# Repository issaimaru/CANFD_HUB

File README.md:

# CANFD_HUB
CANFDコントローラ「ひなた」用のハブ<br>
<br>

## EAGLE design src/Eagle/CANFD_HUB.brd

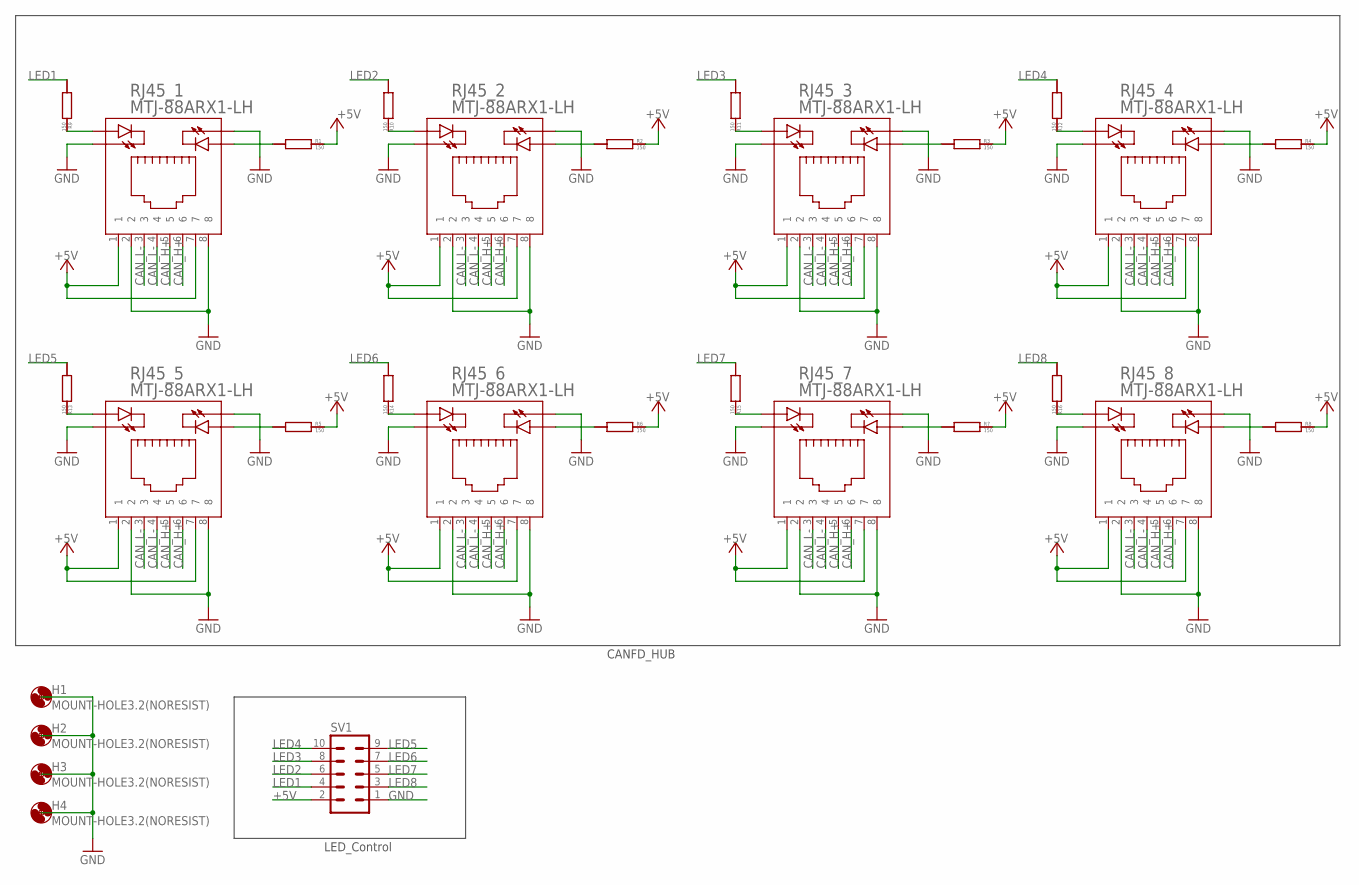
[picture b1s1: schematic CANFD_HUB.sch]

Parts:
H1, H2, H3, H4: MOUNT-HOLE3.2(NORESIST); 3,2
R1, R2, R3, R4, R5, R6, R7, R8, R9, R10, R11, R12, R13, R14, R15, R16: 150; CR0603
RJ45_1, RJ45_2, RJ45_3, RJ45_4, RJ45_5, RJ45_6, RJ45_7, RJ45_8: MTJ-88ARX1-LH
SV1: ML10

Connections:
+5V: R1.RIGHT, R2.RIGHT, R3.RIGHT, R4.RIGHT, R5.RIGHT, R6.RIGHT, R7.RIGHT, R8.RIGHT, RJ45_1.1, RJ45_1.7, RJ45_2.1, RJ45_2.7, RJ45_3.1, RJ45_3.7, RJ45_4.1, RJ45_4.7, RJ45_5.1, RJ45_5.7, RJ45_6.1, RJ45_6.7, RJ45_7.1, RJ45_7.7, RJ45_8.1, RJ45_8.7, SV1.2
CAN_H+: RJ45_1.5, RJ45_1.6, RJ45_2.5, RJ45_2.6, RJ45_3.5, RJ45_3.6, RJ45_4.5, RJ45_4.6, RJ45_5.5, RJ45_5.6, RJ45_6.5, RJ45_6.6, RJ45_7.5, RJ45_7.6, RJ45_8.5, RJ45_8.6
CAN_L-: RJ45_1.3, RJ45_1.4, RJ45_2.3, RJ45_2.4, RJ45_3.3, RJ45_3.4, RJ45_4.3, RJ45_4.4, RJ45_5.3, RJ45_5.4, RJ45_6.3, RJ45_6.4, RJ45_7.3, RJ45_7.4, RJ45_8.3, RJ45_8.4
GND: H1.P$1, H2.P$1, H3.P$1, H4.P$1, RJ45_1.2, RJ45_1.8, RJ45_1.LED1_K, RJ45_1.LED2_K, RJ45_2.2, RJ45_2.8, RJ45_2.LED1_K, RJ45_2.LED2_K, RJ45_3.2, RJ45_3.8, RJ45_3.LED1_K, RJ45_3.LED2_K, RJ45_4.2, RJ45_4.8, RJ45_4.LED1_K, RJ45_4.LED2_K, RJ45_5.2, RJ45_5.8, RJ45_5.LED1_K, RJ45_5.LED2_K, RJ45_6.2, RJ45_6.8, RJ45_6.LED1_K, RJ45_6.LED2_K, RJ45_7.2, RJ45_7.8, RJ45_7.LED1_K, RJ45_7.LED2_K, RJ45_8.2, RJ45_8.8, RJ45_8.LED1_K, RJ45_8.LED2_K, SV1.1
LED1: R9.LEFT, SV1.4
LED2: R10.LEFT, SV1.6
LED3: R11.LEFT, SV1.8
LED4: R12.LEFT, SV1.10
LED5: R13.LEFT, SV1.9
LED6: R14.LEFT, SV1.7
LED7: R15.LEFT, SV1.5
LED8: R16.LEFT, SV1.3
unnamed: R2.LEFT, RJ45_2.LED2_A
unnamed: R1.LEFT, RJ45_1.LED2_A
unnamed: R3.LEFT, RJ45_3.LED2_A
unnamed: R4.LEFT, RJ45_4.LED2_A
unnamed: R5.LEFT, RJ45_5.LED2_A
unnamed: R6.LEFT, RJ45_6.LED2_A
unnamed: R7.LEFT, RJ45_7.LED2_A
unnamed: R8.LEFT, RJ45_8.LED2_A
unnamed: R9.RIGHT, RJ45_1.LED1_A
unnamed: R10.RIGHT, RJ45_2.LED1_A
unnamed: R11.RIGHT, RJ45_3.LED1_A
unnamed: R12.RIGHT, RJ45_4.LED1_A
unnamed: R13.RIGHT, RJ45_5.LED1_A
unnamed: R14.RIGHT, RJ45_6.LED1_A
unnamed: R15.RIGHT, RJ45_7.LED1_A
unnamed: R16.RIGHT, RJ45_8.LED1_A

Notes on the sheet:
LED_Control
CANFD_HUB

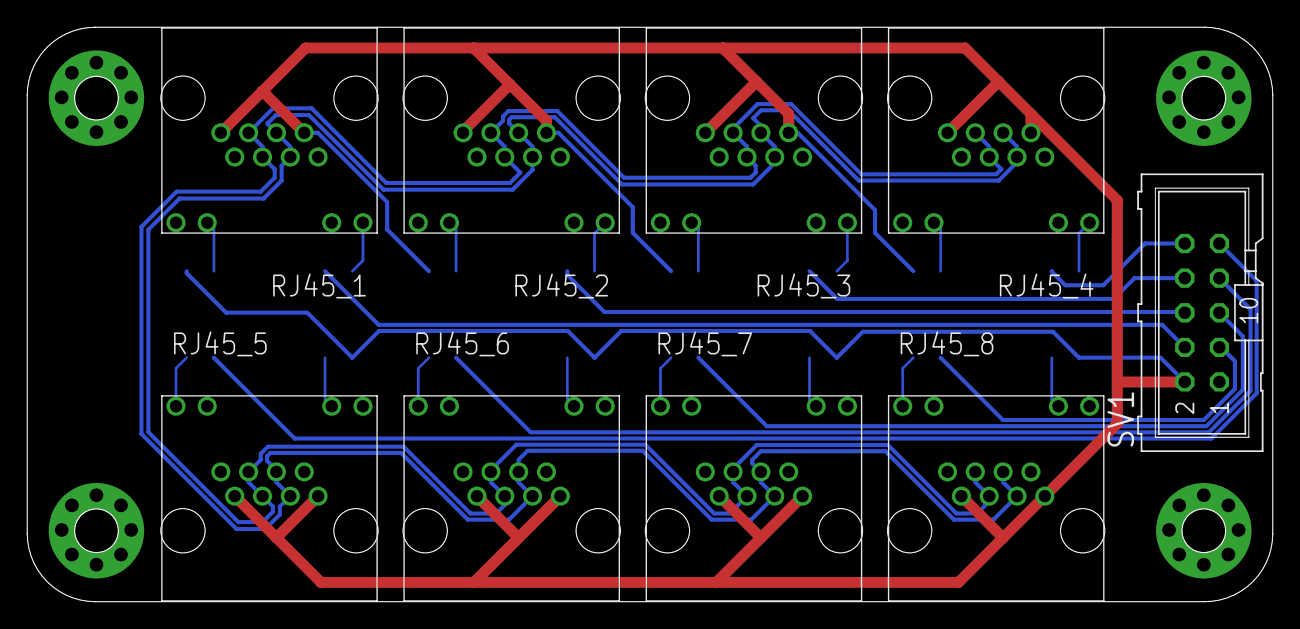
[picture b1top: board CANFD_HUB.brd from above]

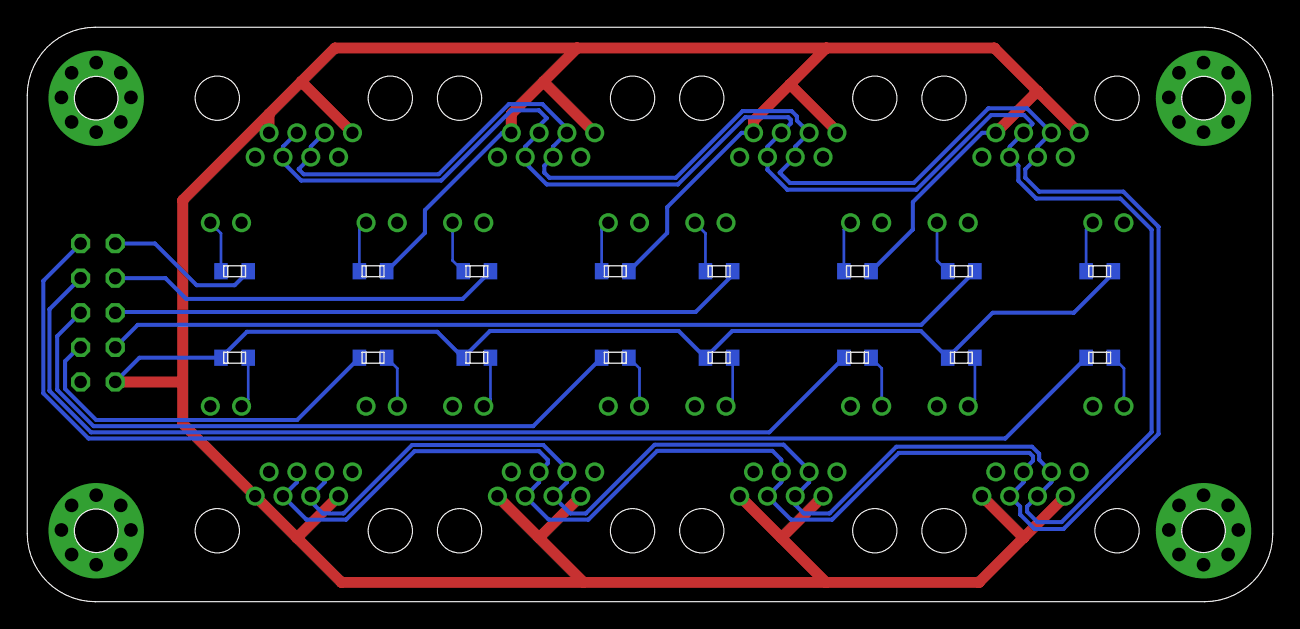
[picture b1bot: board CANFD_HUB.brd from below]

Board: 2 copper layers, 91.4 x 42.2 mm, 29 parts (16 on the bottom side), 28 nets.

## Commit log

2023-06-15 [complete]sch
2023-06-16 [complete]CANFD_HUB
